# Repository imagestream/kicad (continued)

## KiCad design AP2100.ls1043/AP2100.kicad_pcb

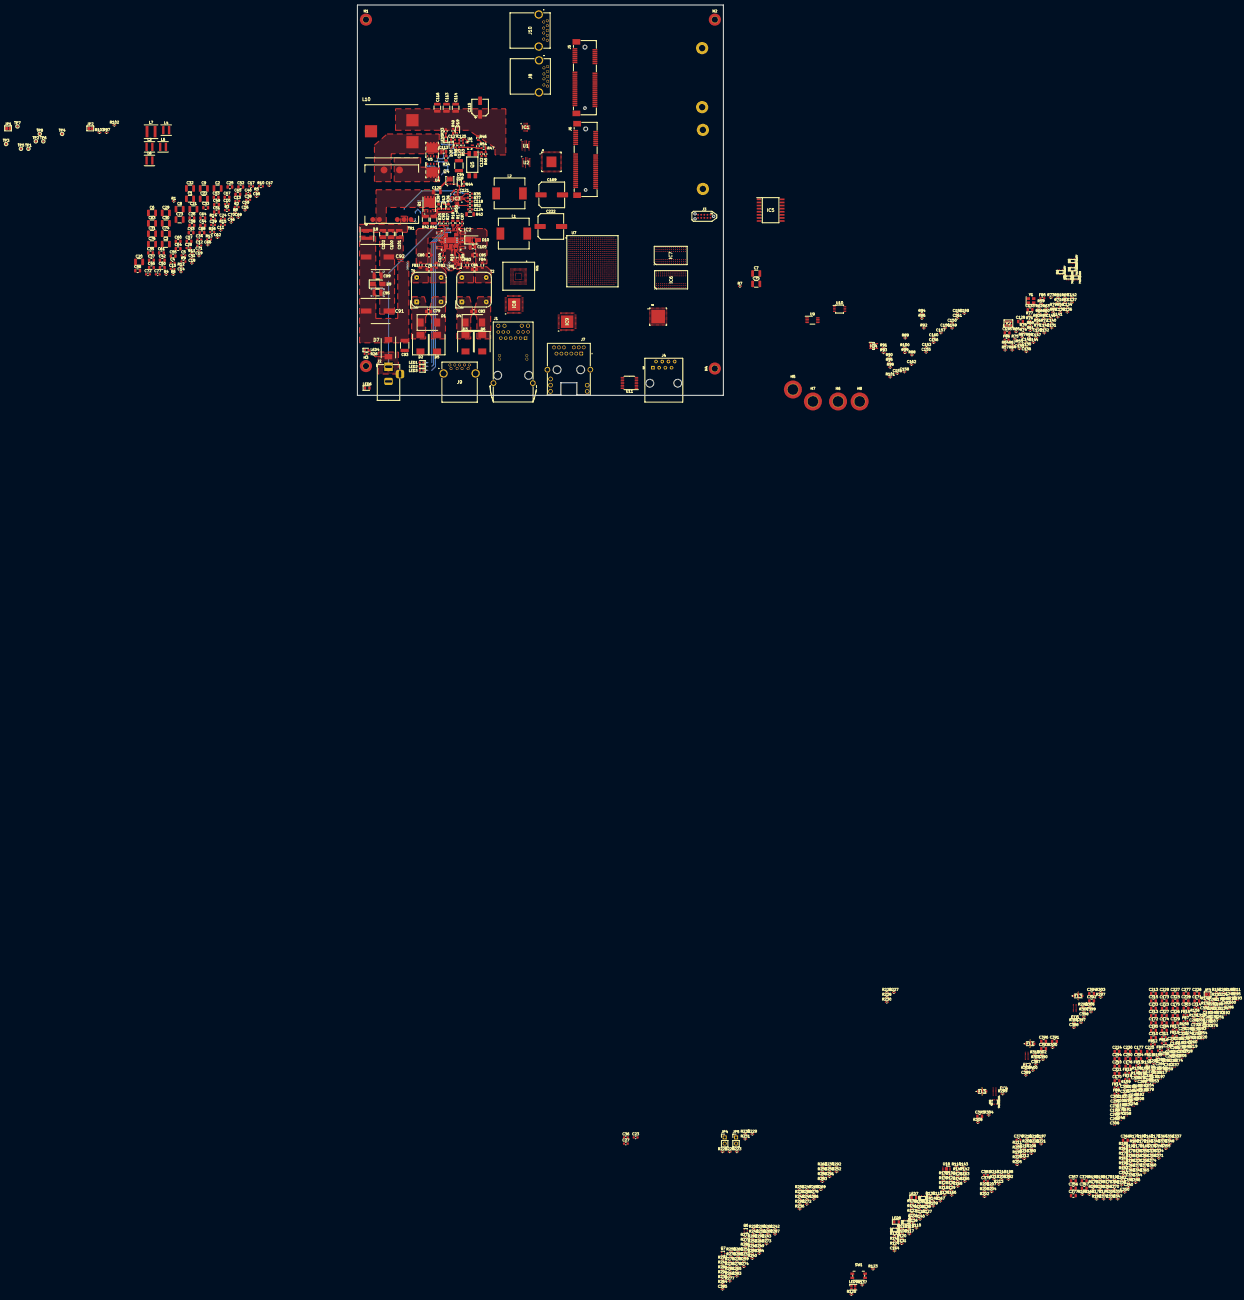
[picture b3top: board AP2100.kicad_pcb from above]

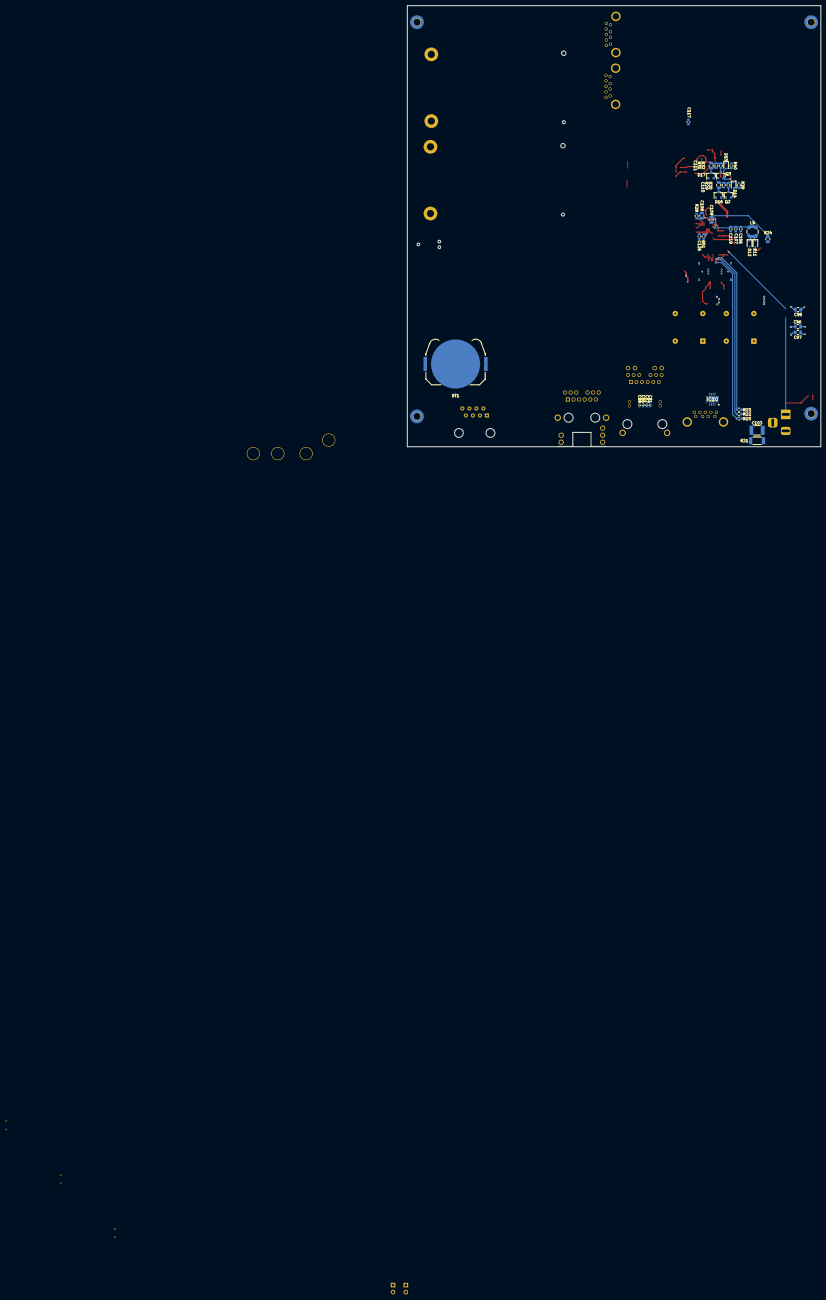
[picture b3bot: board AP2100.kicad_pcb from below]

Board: 6 copper layers, 150.0 x 160.0 mm, 854 parts (41 on the bottom side), 547 nets.

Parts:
BT1: CR2032; BatteryHolder_Keystone_3034_1x20mm
C1, C2, C3, C6, C7, C20, C21, C22, C29, C30, C73, C74: 22uF; C_1210_3225Metric
C4, C5, C12, C13, C15, C24, C28, C38, C39, C40, C72: .1uF; C_0603_1608Metric
C8, C9, C31, C32, C75: 100uF; C_1210_3225Metric
C10, C34: 500pF; C_0603_1608Metric
C11, C14, C16, C19, C69, C70, C135, C137, C139, C141, C331, C332, C333, C334: 1uF; C_0402_1005Metric
C17, C311, C314: .47uF; C_0603_1608Metric
C18: .22uF; C_0402_1005Metric
C23, C27, C36: 47uF; C_0603_1608Metric
C25, C26, C33, C42, C43, C44, C45, C60, C61, C310, C313, C366: 4.7uF; C_0805_2012Metric
C35, C37: DNS 4.7uF; C_0805_2012Metric
C41, C46, C47, C48, C59, C62, C66, C71, C81, C82, C86, C88, C129, C130, C131, C132, C134, C136, C138, C140, C142, C149, C151, C152, C153, C154, C155, C156, C157, C158, C159, C160, C161, C162, C163, C164, C165, C166, C167, C168, C335, C336, C337, C338, C339, C340, C341, C342, C343, C344, C345, C346, C347, C348, C349, C350, C351, C352, C353, C354, C355, C358, C359, C360, C361, C362, C363, C364, C365, C368, C369, C370, C371, C372, C373, C374, C375, C380, C382, C383, C384, C385, C386, C387, C388, C389, C390, C397, C398, C399, C400: .1uF; C_0402_1005Metric
C49, C50, C51, C52, C53, C54, C55, C56, C57, C58, C64, C65, C67, C68, C170, C171, C172, C173, C174, C175, C176, C177, C184, C185, C210, C223, C224, C225, C226, C227, C228, C229, C230, C233, C250, C277, C294, C303, C304, C315, C326, C391, C393, C395: 22uF; C_0805_2012Metric
C63, C76: 2.2uF; C_1210_3225Metric
C77: 5600pF; C_0603_1608Metric
C78, C80, C84, C85: 33nF; C_0805_2012Metric
C79, C83, C97, C98, C108, C109, C112: 1nF; C_0805_2012Metric
C87, C89, C118: 10nF; C_0603_1608Metric
C90: 1nF; C_0603_1608Metric
C91, C92: 33uF; CAPAE1030X1050N
C93, C103: 2.2nF; C_1812_4532Metric
C94: 2200pF; C_1812_4532Metric
C95, C99, C100, C101, C102: 4.7uF; C_1210_3225Metric
C96: 100nF; C_0805_2012Metric
C104: 1.5nF; C_0603_1608Metric
C105: 10nF; C_0805_2012Metric
C106, C127: 2.2uF 25V; C_0603_1608Metric
C107, C117, C119, C121, C122, C126: 100nF; C_0603_1608Metric
C110, C111: 100pF; C_0805_2012Metric
C113, C114, C116: 47uF; C_1210_3225Metric
C115: 100uF; CP_Elec_6.3x5.9
C120: 47nF; C_1206_3216Metric
C123: 220pF; C_0603_1608Metric
C124: 100pF; C_0603_1608Metric
C125: 22nF; C_0603_1608Metric
C128, C133, C213, C321, C323, C327, C329, C356, C357, C367, C376, C377, C392, C394, C396: 10uF; C_0805_2012Metric
C143, C144: 6.8pF; C_0402_1005Metric
C145: DNS 10uF; C_0805_2012Metric
C146, C147, C148: DNS .1uF; C_0402_1005Metric
C150: 1000pF; C_0402_1005Metric
C169, C222: 470uF; C_Elec_10x10.2
C178, C179, C180, C181, C182, C183, C186, C187, C188, C189, C190, C191, C192, C193, C194, C195, C196, C197, C198, C199, C200, C201, C202, C203, C204, C205, C206, C207, C208, C209, C211, C212, C214, C218, C219, C220, C221, C231, C232, C237, C238, C239, C240, C241, C242, C243, C244, C245, C246, C247, C249, C254, C255, C256, C257, C258, C259, C260, C261, C262, C263, C264, C265, C266, C267, C268, C269, C270, C271, C273, C274, C275, C278, C279, C284, C285, C286, C287, C288, C289, C290, C291, C295, C296, C300, C301, C307, C308, C316, C317, C318, C325: .1uF; C_0201_0603Metric
C215, C216, C217, C234, C235, C236, C248, C251, C252, C253, C272, C276, C283: 1500pF; C_0201_0603Metric
C280, C281, C293, C298, C302, C305, C320: 2.2uF; C_0402_1005Metric
C282, C297, C299, C306, C309, C312, C319: 3000pF; C_0402_1005Metric
C292: 1500pF; C_0402_1005Metric
C322, C324, C328, C330: 1uF; C_0201_0603Metric
C378, C379, C381: 2.2uF; C_0603_1608Metric
D1, D2, D3, D4, D5, D6: SM15T68CA; D_SMC
D7: STPS4S200S; DIOM8059X265N
D8: BAV70; SOT-23
D9, D10: SMAJ58A; D_SMA
D11, D12, D13, D14, D15: BAS16J; D_SOD-323
D16: BZX84C10LT1G; SOT-23
D17: BZX84C10; SOT-23
D18, D19, D20: BAS70; D_SOD-323
FB1, FB2, FB3, FB4: 220 OHM; L_0805_2012Metric
FB5: 600 OHM 500mA; L_0603_1608Metric
FB6: DNS 120 OHM 3A; L_0603_1608Metric
FB7, FB8, FB9, FB10, FB11, FB12, FB13, FB14, FB15, FB16, FB17, FB18, FB19: 120 OHM 3A; L_0603_1608Metric
FL1, FL3, FL5: NFE31PT222Z1E9L; NFE31
FL2, FL4, FL6: ACM2012-900-2P-T002; ACM2012_1
H1, H2, H3, H4: Mounting Hole; MountingHole_2.5mm_Pad_TopBottom
H5, H6, H7, H8: FlatAntenna; MountingHole_4.4mm_Pad_TopOnly
IC1: MAX17632BATE+; QFN50P300X300X80-17N
IC2: PM8805TR
IC3: PM8804TR; QFN50P340X340X90-17N
IC4: MIC2774N-29YM5-TR; SOT95P280X145-5N
IC5: PCF2129T_2,518; SOIC127P1032X265-16N
IC6, IC7: AS4C256M16D4-75BCN; BGA96C80P9X16_750X1350X120
IC8, IC9: KSZ9131RNXC; QFN50P700X700X90-49N
IC10: MAX1564ETE+; QFN65P400X400X80-17N
J1: 0826-1X1T-GH-F; BEL_0826-1X1T-GH-F
J2: Barrel_Jack; BarrelJack_Horizontal
J3: Conn_ARM_JTAG_SWD_10; Tag-Connect_TC2050-IDC-NL_2x05_P1.27mm_Vertical
J4: RJ45; RJ45_Amphenol_54602-x08_Horizontal
J5, J6: Bus_PCI_Express_Mini; BUS_PCI_Express_Mini_Full
J7: L836-1J1T-43; BEL_L836-1J1T-43
J8, J9, J10: SS-52000-001; SS52000001
JP1, JP2, JP3: SolderJumper_2_Open; SolderJumper-2_P1.3mm_Open_TrianglePad1.0x1.5mm
JP4, JP5: Jumper_2_Open; PinHeader_1x02_P2.54mm_Vertical
L1, L2: .56uH; L_13.5x12.5mm_H6mm
L3, L5, L6: 1.5uH; L_Coilcraft_XxL4040
L4: 0.6uH; L_Coilcraft_XxL4040
L7: 10uH; L_Coilcraft_XAL5030
L8: 5.6uH; L_Coilcraft_XAL5030
L9: 1mH; L_Coilcraft_LPS4018
L10: 10uH; WE-HCF_201322
LED1: T2; LED_0603_1608Metric
LED2: T1; LED_0603_1608Metric
LED3: T0; LED_0603_1608Metric
LED4: AUX; LED_0603_1608Metric
LED5: +12V; LED_0603_1608Metric
LED6: PWRLED; LED_0805_2012Metric
LED7: WIFI1_LED; LED_0805_2012Metric
LED8: WIFI2_LED; LED_0805_2012Metric
LED9: STATUS LED; LED_Cree-PLCC4_2x2mm_CW
Q1: BSC190N15NS3GATMA1; TRANS_BSC100N06LS3GATMA1
Q2, Q3: PBSS4240T; SOT-23
Q4: FDMC86259P; FDMC86160
Q5: FOD817AS; SOP254P1016X385-4N
Q6, Q7: NTA4151P; SOT-416
R1: 50K; R_0402_1005Metric
R2, R13, R27, R28, R33, R39, R40, R44: 10K; R_0603_1608Metric
R3: 90K; R_0603_1608Metric
R4, R5, R7, R81, R82, R86, R91, R107, R108, R114, R115, R122, R197, R198, R199, R200, R201, R202, R203, R204, R205, R206, R226, R231, R247, R253, R254, R255, R259, R279, R283, R284, R285, R288: 10K; R_0402_1005Metric
R6, R8, R77, R78, R103, R104, R105, R106, R123, R125, R126, R127, R128, R131, R133, R134, R138, R139, R140, R143, R145, R191, R223, R224, R227, R228, R229, R232, R233, R269, R297, R303, R306: 0; R_0402_1005Metric
R9, R15: 30.1K; R_0603_1608Metric
R10, R16: 6.98K; R_0603_1608Metric
R11: 499K; R_0402_1005Metric
R12, R248, R280, R298, R299: 100K; R_0402_1005Metric
R14: 3.74K; R_0603_1608Metric
R17: 36.5; R_0805_2012Metric
R18: 150; R_0805_2012Metric
R19: 26.1K; R_0603_1608Metric
R20, R22, R23: 3.9K; R_0603_1608Metric
R21: 0; R_2010_5025Metric
R24, R36: 10; R_0805_2012Metric
R25: 100K; R_0603_1608Metric
R26, R53: 4.7K; R_0603_1608Metric
R29, R31: 1K; R_0603_1608Metric
R30, R32: 22; R_0603_1608Metric
R34: 18; R_0805_2012Metric
R35: 91K; R_0603_1608Metric
R37: 330K; R_0603_1608Metric
R38: 10K; R_0805_2012Metric
R41: 0R05; R_1210_3225Metric
R42: R100; R_1210_3225Metric
R43: 0; R_1206_3216Metric
R45, R46: 0; R_0603_1608Metric
R47: 20K; R_0603_1608Metric
R48, R50: 2K; R_0603_1608Metric
R49: 47K; R_0603_1608Metric
R51: 390; R_0603_1608Metric
R52: 130K; R_0603_1608Metric
R54: 5.23K; R_0603_1608Metric
R55, R75: 82; R_0402_1005Metric
R56, R76, R85: 110; R_0402_1005Metric
R57, R58, R59, R60, R61, R63, R72, R73, R158, R159: 10; R_0402_1005Metric
R62, R70, R71, R74: 1; R_0402_1005Metric
R64, R65, R66, R67, R68, R69: 49.9; R_0402_1005Metric
R79, R80: 33; R_0402_1005Metric
R83: 75; R_0402_1005Metric
R84: 56; R_0402_1005Metric
R87: DNS 10K; R_0402_1005Metric
R88, R89, R90, R97, R100, R102, R109, R110, R111, R112, R113, R116, R117, R120, R135, R171, R179, R187, R208, R210, R211, R212, R213, R214, R215, R217, R218, R220, R234, R235, R239, R240, R252, R260: 4.7K; R_0402_1005Metric
R92, R93, R94, R95, R96, R98, R101, R119, R129, R221, R222, R245, R249, R265, R266, R267, R277, R281, R293, R294, R296, R301, R304, R307, R309, R310: 1K; R_0402_1005Metric
R99, R118: DNP 4.7K; R_0402_1005Metric
R121, R130, R132: DNP 0; R_0402_1005Metric
R124, R137: 91K; R_0402_1005Metric
R136, R148, R149, R150, R151, R154: 330; R_0402_1005Metric
R141, R142, R144, R146, R147, R243, R244, R275, R276: 220; R_0402_1005Metric
R152, R153: 0R33; R_0402_1005Metric
R155, R156, R157, R160: 5.1; R_0402_1005Metric
R161, R162: 240; R_0402_1005Metric
R163, R164: 36; R_0402_1005Metric
R165, R166, R167, R168, R169, R170, R172, R173, R174, R176, R177, R178, R180, R181, R182, R183, R185, R186, R188, R189, R190, R192, R193, R194, R195, R196: 39; R_0402_1005Metric
R175, R184: 162; R_0402_1005Metric
R207, R209, R216: DNS 4.7K; R_0402_1005Metric
R219: 2K; R_0402_1005Metric
R225, R230: 2.7K; R_0402_1005Metric
R236, R237, R238, R241, R242, R246, R270, R271, R272, R273, R274, R278: 22; R_0402_1005Metric
R250: 698; R_0402_1005Metric
R251, R302, R305, R308: 200; R_0402_1005Metric
R256, R257, R258, R286, R287, R289: DNP 10K; R_0402_1005Metric
R261, R282: 6.04K; R_0402_1005Metric
R262, R263, R264, R268, R290, R291, R292, R295: DNP 1K; R_0402_1005Metric
R300: 26.1K; R_0402_1005Metric
SW1: RESET; Panasonic_EVQPUJ_EVQPUA
T1, T2: RN102-2-02-1M1; Choke_Schaffner_RN102-04-14.0x14.0mm
TP1, TP2, TP3, TP4, TP5, TP6, TP7, TP8: TestPoint; TestPoint_Pad_D1.0mm
TR1: POE120PL-12L; Transformer_Coilcraft_POE120PL
U1, U2: MPQ8634AGLE-P; QFN45P300X400X100-21N
U3: MC34VR500V4ES; QFN50P800X800X90-57N
U4, U5: STL90N6F7; TRANS_STL60P4LLF6
U6: TS2431-AILT; SOT-23-3
U7: LS1043ASE7xxx; BGA621C80P25X25_2100X2100X192N
U8: 6V49205BNLGI; QFP50P700X700X90-49N
U9: 74LVC2G08; VSSOP-8_3.0x3.0mm_P0.65mm
U10: SA56004EDP,118; TSSOP-8_3x3mm_P0.65mm
U11: SP3232EBEY-L/TR; TSSOP-16_4.4x5mm_P0.65mm
U12, U13, U16, U19: 74LVC1G08; SC70
U14, U15, U17, U20: 74LVC1G07; SC70
U18: ATECC608A-MAHDA; DFN-8-1EP_3x2mm_P0.5mm_EP1.3x1.5mm
U21: EMMC04G-M627-A01; BGA153N50P14X14_1300X1150X100N
U22: 74LVC2G04; SC70-6
U23, U24, U25: SP3011; uDFN-14_1.35x3.5mm_P0.5mm
Y1: 25 MHz; Crystal_SMD_3225-4Pin_3.2x2.5mm
Y2: DNS AX3DAF1-156.2500; AX3DCF11562500

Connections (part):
/1V5: C53.2, C54.2, C55.2, C56.2, C57.2, C58.2, J5.6 (+1V5), J5.28 (+1V5), J5.48 (+1V5), J6.6 (+1V5), J6.28 (+1V5), J6.48 (+1V5), L4.1, U3.13 (FB1)
/1V8: C67.2, C68.2, C151.1, C161.1, C162.1, C163.1, C164.1, C166.1, C167.1, C168.1, C178.2, C179.2, C180.2, C181.2, C182.2, C183.2, C184.2, C185.2, C209.2, C210.2, C212.1, C213.2, C379.2, C380.1, FB7.1, FB8.1, FB19.1, J3.1 (VTref), JP1.1, JP2.2, L6.1, R88.1, R89.1, R90.1, R91.2, R96.1, R97.1, R98.1, R100.2, R101.2, R107.2, R108.2, R109.2, R110.2, R111.2, R112.2, R113.2, R114.2, R115.2, R116.2, R117.2, R118.1, R119.2, R122.2, R129.2, R137.2, R149.1, R155.1, R156.1, R157.1, R160.1, R197.1, R198.1, R199.1, R200.1, R201.1, R202.1, R203.1, R204.1, R205.1, R206.1, R207.1, R208.1, R209.1, R221.1, R222.1, U3.25 (FB2), U7.J12 (OVDD1), U7.J13 (OVDD2), U7.J14 (OVDD3)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
/2V5_VPP: C33.2, C331.1, C332.1, C333.1, C334.1, IC6.B1 (VPP_1), IC6.R9 (VPP_2), IC7.B1 (VPP_1), IC7.R9 (VPP_2), U3.28 (LDO3)
/3V3: C11.2, C14.2, C23.2, C27.2, C28.2, C29.2, C30.2, C31.2, C32.2, C34.1, C36.2, C41.2, C42.2, C43.2, C44.2, C45.2, C46.2, C47.2, C48.2, C59.2, C60.2, C61.2, C62.2, C134.1, C149.1, C152.1, C157.1, C158.1, C160.1, C165.1, C231.2, C232.2, C233.2, C381.2, C382.1, C387.1, FB5.2, FB6.1, FB17.1, FB18.1, IC4.5 (VDD), IC5.16 (VDD), IC8.1 (AVDDH_1), IC8.12 (AVDDH_2), IC8.16 (DVDDH_1), IC8.34 (DVDDH_2), IC8.40 (DVDDH_3), IC9.1 (AVDDH_1), IC9.12 (AVDDH_2), IC9.16 (DVDDH_1), IC9.34 (DVDDH_2), IC9.40 (DVDDH_3), J1.18 (LEDY+), J1.19 (LEDG-_O+), J5.2 (+3V3AUX), J5.24 (+3V3AUX), J5.39 (+3V3AUX), J5.41 (+3V3AUX), J5.52 (+3V3AUX), J6.2 (+3V3AUX), J6.24 (+3V3AUX), J6.39 (+3V3AUX), J6.41 (+3V3AUX), J6.52 (+3V3AUX), J7.14, J7.16, L2.2, LED9.4 (A), Q6.2 (S), Q7.2 (S), R4.2, R5.1, R13.2, R81.1, R82.1, R92.2, R93.2, R94.2, R95.2, R124.2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
/3V3_PG: R126.1, U2.9 (PGOOD)
/5V: C73.1, C74.1, C75.2, C390.1, IC1.6 (FB), IC1.9 (EXTVCC), IC10.1 (INA), IC10.2 (VCC), IC10.3 (INB), IC10.4 (INC), IC10.5 (SEL), JP4.2 (B), JP5.2 (B), L7.2
/5V_PG: IC1.8 (~RESET), R127.1
/12V: C1.1, C2.1, C3.1, C20.1, C21.1, C22.1, C63.1, C113.1, C114.1, C115.1, C116.1, C117.1, D19.1 (K), IC1.1 (EN/UVLO), IC1.15 (VIN_1), IC1.16 (VIN_2), L10.2, R11.2, R33.2, R46.1, R49.2, U1.10 (VIN_1), U1.21 (VIN_2), U2.10 (VIN_1), U2.21 (VIN_2)
/25MHZ_CPLD: R83.2, R85.2
/25MHZ_EC1_RGMII: IC8.46 (XI), R80.2
/25MHZ_EC2_RGMII: IC9.46 (XI), R79.2
/125M_CLK: R84.2, U7.AA3 (EC1_GTX_CLK125), U7.AE4 (EC2_GTX_CLK125)
/CPU Power/EVDD: C249.2, C250.2, FB7.2, U7.M8 (EVDD)
/CPU_VDD_PG: R125.1, U1.9 (PGOOD)
/CPU_VDD_SENSE: C5.2, C6.2, C7.2, C8.2, C9.2, C10.1, C215.2, C216.2, C217.2, C218.2, C219.2, C220.2, C221.2, C222.1, C223.2, C224.2, C225.2, C226.2, C227.2, C228.2, C229.2, C230.2, C234.2, C235.2, C236.2, C237.2, C238.2, C239.2, C240.2, C241.2, C242.2, C243.2, C244.2, C245.2, C246.2, C247.2, C248.2, C251.2, C252.2, C253.2, C254.2, C255.2, C256.2, C257.2, C258.2, C259.2, C260.2, C261.2, C262.2, C263.2, C264.2, C265.2, C266.2, C267.2, C268.2, C269.2, C270.2, C271.2, C272.2, C315.2, C316.2, FB9.1, FB11.1, FB13.1, FB14.1, FB15.1, FB16.1, JP3.2 (B), L1.2, R2.2, R102.1, R154.2, R159.2, U7.H20 (TA_BB_VDD), U7.K13 (VDD01), U7.K15 (VDD02), U7.K17 (VDD03), U7.L10 (VDD04), U7.L12 (VDD05), U7.L14 (VDD06)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
/DDR4 Memory/ALERT_B: IC6.P9 (ALERT#), IC7.P9 (ALERT#), R191.2
/DDR4 Memory/DDR4_A0: IC6.P3 (A0), IC7.P3 (A0), R168.1, U7.AC25 (D1_MA00)
/DDR4 Memory/DDR4_A1: IC6.P7 (A1), IC7.P7 (A1), R169.1, U7.AA21 (D1_MA01)
/DDR4 Memory/DDR4_A2: IC6.R3 (A2), IC7.R3 (A2), R170.1, U7.V23 (D1_MA02)
/DDR4 Memory/DDR4_A3: IC6.N7 (A3), IC7.N7 (A3), R172.1, U7.AD23 (D1_MA03)
/DDR4 Memory/DDR4_A4: IC6.N3 (A4), IC7.N3 (A4), R173.1, U7.AA23 (D1_MA04)
/DDR4 Memory/DDR4_A5: IC6.P8 (A5), IC7.P8 (A5), R174.1, U7.W23 (D1_MA05)
/DDR4 Memory/DDR4_A6: IC6.P2 (A6), IC7.P2 (A6), R176.1, U7.AC24 (D1_MA06)
/DDR4 Memory/DDR4_A7: IC6.R8 (A7), IC7.R8 (A7), R177.1, U7.U24 (D1_MA07)
/DDR4 Memory/DDR4_A8: IC6.R2 (A8), IC7.R2 (A8), R178.1, U7.R22 (D1_MA08)
/DDR4 Memory/DDR4_A9: IC6.R7 (A9), IC7.R7 (A9), R180.1, U7.W22 (D1_MA09)
/DDR4 Memory/DDR4_A10: IC6.M3 (A10/AP), IC7.M3 (A10/AP), R181.1, U7.AB23 (D1_MA10)
/DDR4 Memory/DDR4_A11: IC6.T2 (A11), IC7.T2 (A11), R182.1, U7.T23 (D1_MA11)
/DDR4 Memory/DDR4_A12: IC6.M7 (A12/BC#), IC7.M7 (A12/BC#), R183.1, U7.AC23 (D1_MA12)
/DDR4 Memory/DDR4_A13: IC6.T8 (A13), IC7.T8 (A13), R185.1, U7.T25 (D1_MA13)
/DDR4 Memory/DDR4_A15: IC6.L3 (ACT#), IC7.L3 (ACT#), R186.1, U7.U21 (D1_MA15/!MACT)
/DDR4 Memory/DDR4_BA0: IC6.N2 (BA0), IC7.N2 (BA0), R165.1, U7.AC21 (D1_MBA0)
/DDR4 Memory/DDR4_BA1: IC6.N8 (BA1), IC7.N8 (BA1), R166.1, U7.Y23 (D1_MBA1)
/DDR4 Memory/DDR4_BA2: IC6.M2 (BG0), IC7.M2 (BG0), R167.1, U7.AE23 (D1_MBA2/MBG0)
/DDR4 Memory/DDR4_CAS_B: IC6.M8 (CAS#/A15), IC7.M8 (CAS#/A15), R189.1, U7.AC22 (~D1_MCAS~)
/DDR4 Memory/DDR4_CKE0: IC6.K2 (CKE), IC7.K2 (CKE), R192.1, U7.W21 (D1_MCKE0)
/DDR4 Memory/DDR4_CKE1: R193.1, U7.AB21 (D1_MCKE1)
/DDR4 Memory/DDR4_CLK_N: IC6.K8 (CK#), IC7.K8 (CK#), R163.1, U7.AA25 (~D1_MCK0~)
/DDR4 Memory/DDR4_CLK_P: IC6.K7 (CK), IC7.K7 (CK), R164.1, U7.AA24 (D1_MCK0)
/DDR4 Memory/DDR4_CS0_B: IC6.L7 (CS#), IC7.L7 (CS#), R195.1, U7.U23 (~D1_MCS0~)
/DDR4 Memory/DDR4_DM0: IC6.E7 (LDM#/LDBI#), U7.L25 (D1_MDM0)
/DDR4 Memory/DDR4_DM1: IC6.E2 (UDM#/UDBI#), U7.L21 (D1_MDM1)
/DDR4 Memory/DDR4_DM2: IC7.E7 (LDM#/LDBI#), U7.E23 (D1_MDM2)
/DDR4 Memory/DDR4_DM3: IC7.E2 (UDM#/UDBI#), U7.G23 (D1_MDM3)
/DDR4 Memory/DDR4_DQ0: IC6.G2 (DQ0), U7.J25 (D1_MDQ00)
/DDR4 Memory/DDR4_DQ1: IC6.F7 (DQ1), U7.K24 (D1_MDQ01)
/DDR4 Memory/DDR4_DQ2: IC6.H3 (DQ2), U7.N24 (D1_MDQ02)
/DDR4 Memory/DDR4_DQ3: IC6.H7 (DQ3), U7.R24 (D1_MDQ03)
/DDR4 Memory/DDR4_DQ4: IC6.H2 (DQ4), U7.H24 (D1_MDQ04)
/DDR4 Memory/DDR4_DQ5: IC6.H8 (DQ5), U7.K25 (D1_MDQ05)
/DDR4 Memory/DDR4_DQ6: IC6.J3 (DQ6), U7.N25 (D1_MDQ06)
/DDR4 Memory/DDR4_DQ7: IC6.J7 (DQ7), U7.P25 (D1_MDQ07)
/DDR4 Memory/DDR4_DQ8: IC6.A3 (DQ8), U7.L23 (D1_MDQ08)
/DDR4 Memory/DDR4_DQ9: IC6.B8 (DQ9), U7.M23 (D1_MDQ09)
/DDR4 Memory/DDR4_DQ10: IC6.C3 (DQ10), U7.N21 (D1_MDQ10)
/DDR4 Memory/DDR4_DQ11: IC6.C7 (DQ11), U7.P21 (D1_MDQ11)
/DDR4 Memory/DDR4_DQ12: IC6.C2 (DQ12), U7.K21 (D1_MDQ12)
/DDR4 Memory/DDR4_DQ13: IC6.C8 (DQ13), U7.L22 (D1_MDQ13)
/DDR4 Memory/DDR4_DQ14: IC6.D3 (DQ14), U7.M21 (D1_MDQ14)
/DDR4 Memory/DDR4_DQ15: IC6.D7 (DQ15), U7.P23 (D1_MDQ15)
/DDR4 Memory/DDR4_DQ16: IC7.G2 (DQ0), U7.C24 (D1_MDQ16)
/DDR4 Memory/DDR4_DQ17: IC7.F7 (DQ1), U7.C25 (D1_MDQ17)
/DDR4 Memory/DDR4_DQ18: IC7.H3 (DQ2), U7.F24 (D1_MDQ18)
/DDR4 Memory/DDR4_DQ19: IC7.H7 (DQ3), U7.H25 (D1_MDQ19)
/DDR4 Memory/DDR4_DQ20: IC7.H2 (DQ4), U7.B24 (D1_MDQ20)
/DDR4 Memory/DDR4_DQ21: IC7.H8 (DQ5), U7.D24 (D1_MDQ21)
/DDR4 Memory/DDR4_DQ22: IC7.J3 (DQ6), U7.F25 (D1_MDQ22)
/DDR4 Memory/DDR4_DQ23: IC7.J7 (DQ7), U7.G25 (D1_MDQ23)
/DDR4 Memory/DDR4_DQ24: IC7.A3 (DQ8), U7.F22 (D1_MDQ24)
/DDR4 Memory/DDR4_DQ25: IC7.B8 (DQ9), U7.H21 (D1_MDQ25)
/DDR4 Memory/DDR4_DQ26: IC7.C3 (DQ10), U7.J23 (D1_MDQ26)
/DDR4 Memory/DDR4_DQ27: IC7.C7 (DQ11), U7.K23 (D1_MDQ27)
/DDR4 Memory/DDR4_DQ28: IC7.C2 (DQ12), U7.G21 (D1_MDQ28)
/DDR4 Memory/DDR4_DQ29: IC7.C8 (DQ13), U7.F23 (D1_MDQ29)
/DDR4 Memory/DDR4_DQ30: IC7.D3 (DQ14), U7.J21 (D1_MDQ30)
/DDR4 Memory/DDR4_DQ31: IC7.D7 (DQ15), U7.J22 (D1_MDQ31)
/DDR4 Memory/DDR4_DQS0_N: IC6.F3 (LDQS#), U7.M25 (~D1_MDQS0~)
/DDR4 Memory/DDR4_DQS0_P: IC6.G3 (LDQS), U7.M24 (D1_MDQS0)
/DDR4 Memory/DDR4_DQS1_N: IC6.A7 (UDQS#), U7.N23 (~D1_MDQS1~)
/DDR4 Memory/DDR4_DQS1_P: IC6.B7 (UDQS), U7.N22 (D1_MDQS1)
/DDR4 Memory/DDR4_DQS2_N: IC7.F3 (LDQS#), U7.D25 (~D1_MDQS2~)
/DDR4 Memory/DDR4_DQS2_P: IC7.G3 (LDQS), U7.E25 (D1_MDQS2)
/DDR4 Memory/DDR4_DQS3_N: IC7.A7 (UDQS#), U7.H22 (~D1_MDQS3~)
/DDR4 Memory/DDR4_DQS3_P: IC7.B7 (UDQS), U7.H23 (D1_MDQS3)
/DDR4 Memory/DDR4_ODT0: IC6.K3 (ODT), IC7.K3 (ODT), R194.1, U7.U22 (D1_MODT0)
/DDR4 Memory/DDR4_PAR: IC6.T3 (PAR), IC7.T3 (PAR), R196.1, U7.U25 (D1_MAPAR_OUT)
/DDR4 Memory/DDR4_RAS_B: IC6.L8 (RAS#/A16), IC7.L8 (RAS#/A16), R190.1, U7.AB25 (~D1_MRAS~)
/DDR4 Memory/DDR4_TEN: IC6.N9 (TEN), IC7.N9 (TEN), R179.1
/DDR4 Memory/DDR4_WE_B: IC6.L2 (WE#/A14), IC7.L2 (WE#/A14), R188.1, U7.Y21 (~D1_MWE~)
/DDR4_RST_B: IC6.P1 (RESET#), IC7.P1 (RESET#), R139.2, R171.2
/DDRCLK_18: R75.2, R76.2, U7.F19 (DDRCLK)
/DDR_VREF: C69.2, C336.1, C337.1, C338.1, C339.1, IC6.M1 (VREFCA), IC7.M1 (VREFCA), U3.31 (REFOUT)
/DDR_VTT: C64.2, C65.2, C340.1, C341.1, C342.1, C343.1, C344.1, C345.1, C346.1, C347.1, C358.1, C359.1, C360.1, C361.1, C362.1, C363.1, C364.1, C365.1, C366.1, C367.1, L5.1, R165.2, R166.2, R167.2, R168.2, R169.2, R170.2, R172.2, R173.2, R174.2, R176.2, R177.2, R178.2, R180.2, R181.2, R182.2, R183.2, R185.2, R186.2, R188.2, R189.2, R190.2, R192.2, R193.2, R194.2, R195.2, R196.2, U3.19 (FB4)
/DIFF_SYSCLK_N: R73.2, U7.G9 (~DIFF_SYSCLK~)
/DIFF_SYSCLK_P: R72.2, U7.G8 (DIFF_SYSCLK)
/ETH0_LED1-: J1.20 (LEDG+_O-), R243.2
/ETH0_LED2-: J1.17 (LEDY-), R244.2
/Flash / eMMC/IFC_CLE: R207.2, R219.2, U7.C19 (CFG_RCW_SRC8/IFC_CLE)
/GVDD: C49.2, C50.2, C51.2, C52.2, C66.1, C70.2, C169.1, C170.2, C171.2, C172.2, C173.2, C174.2, C175.2, C176.2, C177.2, C186.2, C187.2, C188.2, C189.2, C190.2, C191.2, C192.2, C193.2, C194.2, C195.2, C196.2, C197.2, C198.2, C199.2, C200.2, C201.2, C202.2, C203.2, C204.2, C205.2, C206.2, C207.2, C208.2, C335.1, C348.1, C349.1, C350.1, C351.1, C352.1, C353.1, C354.1, C355.1, C356.1, C357.1, C368.1, C369.1, C370.1, C371.1, C372.1, C373.1, C374.1, C375.1, C376.1, C377.1, IC6.A1 (VDDQ_1), IC6.A9 (VDDQ_2), IC6.B3 (VDD_1), IC6.B9 (VDD_2), IC6.C1 (VDDQ_3), IC6.D1 (VDD_3), IC6.D9 (VDDQ_4), IC6.F2 (VDDQ_5), IC6.F8 (VDDQ_6), IC6.G1 (VDDQ_7), IC6.G7 (VDD_4), IC6.G9 (VDDQ_8), IC6.J1 (VDD_5), IC6.J2 (VDDQ_9), IC6.J8 (VDDQ_10), IC6.J9 (VDD_6), IC6.L1 (VDD_7), IC6.L9 (VDD_8), IC6.R1 (VDD_9), IC6.T9 (VDD_10), IC7.A1 (VDDQ_1)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
/I2C1_SCL: R8.2, R77.1, R93.1, R103.1, R131.1, R145.1, U7.N1 (IIC1_SCL)
/I2C1_SDA: R6.2, R78.1, R92.1, R104.1, R134.1, R143.1, U7.M1 (IIC1_SDA)
/I2C2_SCL: R95.1, R224.1, U7.K3 (GPIO4_02/IIC2_SCL)
/I2C2_SDA: R94.1, R223.1, U7.L3 (GPIO4_03/IIC2_SDA)
/I2C4_SCL: R229.1, R309.1, U7.M3 (GPIO4_12/USB3_DRWBUS)
/I2C4_SDA: R228.1, R310.1, U7.N3 (GPIO4_13/USB3_PWRFAULT)
/MPCIE0_CLK_N: J5.11 (REFCLK-), R58.2, R67.2
/MPCIE0_CLK_P: J5.13 (REFCLK+), R57.2, R66.2
/MPCIE1_CLK_N: J6.11 (REFCLK-), R60.2, R69.2
/MPCIE1_CLK_P: J6.13 (REFCLK+), R59.2, R68.2
/PMIC_INT_B: R4.1, U3.1 (~INT~), U9.2
/PMIC_POR_B: R130.1, R138.1, U3.3 (~POR~)
/POE_TD1_N: IC8.3 (TXRXM_A), J1.10 (TRD1-)
/POE_TD1_P: IC8.2 (TXRXP_A), J1.11 (TRD1+)
/POE_TD2_N: IC8.6 (TXRXM_B), J1.5 (TRD2-)
/POE_TD2_P: IC8.5 (TXRXP_B), J1.4 (TRD2+)
/POE_TD3_N: IC8.8 (TXRXM_C), J1.2 (TRD3-)
/POE_TD3_P: IC8.7 (TXRXP_C), J1.3 (TRD3+)
/POE_TD4_N: IC8.11 (TXRXM_D), J1.9 (TRD4-)
/POE_TD4_P: IC8.10 (TXRXP_D), J1.8 (TRD4+)
/PWR_X1VDD: C25.2, C294.2, C303.2, C304.2, FB10.2, FB12.2, U3.18 (LDO1)
/PoE Power/IN_12: C80.1, FB1.2, IC2.12 (IN12_1), IC2.15 (IN12_2), IC2.16 (IN12_3), IC2.EP4
/PoE Power/IN_36: C80.2, FB2.2, IC2.19 (IN36_1), IC2.20 (IN36_2), IC2.23 (IN36_3), IC2.EP3
/PoE Power/IN_45: C85.1, FB3.2, IC2.33 (IN45_1), IC2.36 (IN45_2), IC2.37 (IN45_3), IC2.EP2
/PoE Power/IN_78: C85.2, FB4.2, IC2.1 (IN78_1), IC2.40 (IN78_2), IC2.41 (IN78_3), IC2.EP1
/PoE Power/PGD: C108.1, IC2.25 (PGD), IC3.6 (PGD), R28.2
/PoE Power/VB: C87.1, IC2.2 (VB), LED1.2 (A), LED2.2 (A), LED3.2 (A), R28.1
/PoE Power/VDC: C91.1, C92.1, C93.1, C95.1, C96.1, C97.1, C98.1, C99.1, D7.1, D8.2 (A), D9.1 (K), IC2.27 (VOUT_1), IC2.28 (VOUT_2), L8.1
/PoE Power/VOB: C89.2, C105.1, D8.1 (A), D10.1 (A1), IC2.17 (VOB_1), IC2.18 (VOB_2), IC2.29 (VOB_3), IC2.30 (VDD), IC2.38 (VOB_4), IC2.39 (VOB_5), IC2.EP5, IC2.EP6, R19.1
/Power/EN_VDD: C26.2, R1.1, U3.26 (LDO2)
/RST_PCIE0_B: R227.1, U17.4
/RST_PCIE1_B: R232.1, U20.4
/RST_eMMC_B: R140.2, R197.2, U21.K5 (RST_N)
/Reset/JTAG_RST_B_18: J3.10 (~RESET~), R114.1, U13.2
/Reset/PORESET_B_18: R121.1, R137.1, U7.F10 (~PORESET~), U13.4, U14.2, U15.2, U16.1, U19.1
/Reset/RESET_BTN_B: R91.1, SW1.1 (A), U7.L1 (GPIO1_20/!UART2_RTS)
/Reset/RESET_REQ_B_18: R97.2, R128.2, U7.G7 (~RESET_REQ~)
/Reset/RST_PCIE0: U7.K1 (GPIO1_18/UART2_SIN), U16.2
/Reset/RST_PCIE1: U7.L2 (GPIO1_16/UART2_SOUT), U19.2
/Reset/RTC_OUT: IC5.7 (CLKOUT), R129.1, U7.F16 (RTC/GPIO1_14)
/Reset/TABB_RTCCLK: TP2.1, U7.G20 (TA_BB_RTC)
/Reset/THERM_INTn: U9.1, U9.3
/Reset/UART_CTS: U7.J1 (GPIO1_21/!UART1_CTS), U11.9 (R2OUT)
/Reset/UART_RTS: U7.J2 (GPIO1_19/!UART1_RTS), U11.10 (T2IN)
/Reset/UART_RX: U7.H2 (GPIO1_17/UART1_SIN), U11.12 (R1OUT)
/Reset/UART_TX: U7.H1 (GPIO1_15/UART1_SOUT), U11.11 (T1IN)
/S1VDD: C280.2, C281.2, C282.2, C283.2, C284.2, C285.2, C286.2, C287.2, C288.2, FB9.2, FB11.2, R251.1, U7.T15 (S1VDD1), U7.T16 (S1VDD2), U7.T17 (S1VDD3), U7.T18 (S1VDD4), U7.W14 (S1VDD5)
/SD1_REFCLK1_N: C147.2, R240.1, U7.W9 (SD1_REF_CLK1_N)
/SD1_REFCLK1_P: C148.2, R239.1, U7.W10 (SD1_REF_CLK1_P)
/SD1_REFCLK2_N: R63.2, R65.2, U7.AD20 (SD1_REF_CLK2_N)
/SD1_REFCLK2_P: R61.2, R64.2, U7.AE20 (SD1_REF_CLK2_P)
/SD_RX1_N: J5.23 (PERn0), U7.AD15 (SD1_RX1_N)
/SD_RX1_P: J5.25 (PERp0), U7.AE15 (SD1_RX1_P)
/SD_RX2_N: J6.23 (PERn0), U7.AD17 (SD1_RX2_N)
/SD_RX2_P: J6.25 (PERp0), U7.AE17 (SD1_RX2_P)
/SD_TX1_N: J5.31 (PETn0), U7.AB15 (SD1_TX1_N)
/SD_TX1_P: J5.33 (PETp0), U7.AA15 (SD1_TX1_P)
/SD_TX2_N: J6.31 (PETn0), U7.AB17 (SD1_TX2_N)
/SD_TX2_P: J6.33 (PETp0), U7.AA17 (SD1_TX2_P)
/SOC_IRQ0: IC8.38 (INT_N/PME_N2/ALLPHYAD), R90.2, R245.2, U7.F15 (IRQ00)
/SOC_IRQ1: IC9.38 (INT_N/PME_N2/ALLPHYAD), R89.2, R277.2, U7.G15 (IRQ01)
/SYSCLK_18: R55.2, R56.2, U7.F9 (SYSCLK)
/SerDes / RGMII Ethernet/P0_LED1: IC8.17 (LED1/PME_N1//PHYAD0), R243.1, R259.2, R268.1
/SerDes / RGMII Ethernet/P0_LED2: IC8.15 (LED2/PHYAD1), R244.1, R258.2, R267.1
/SerDes / RGMII Ethernet/P0_RXD0: IC8.32 (RXD0/MODE0), R236.2, R256.2, R265.1
/SerDes / RGMII Ethernet/P0_RXD1: IC8.31 (RXD1/MODE1), R237.2, R255.2, R264.1
/SerDes / RGMII Ethernet/P0_RXD2: IC8.28 (RXD2/MODE2), R238.2, R254.2, R263.1
/SerDes / RGMII Ethernet/P0_RXD3: IC8.27 (RXD3/MODE3), R241.2, R253.2, R262.1
/SerDes / RGMII Ethernet/P0_RX_CLK: IC8.35 (RXC/PHYAD2), R246.2, R257.2, R266.1
/SerDes / RGMII Ethernet/P0_RX_CTL/CLK125_EN: IC8.33 (RX_CTL/CLK125_EN), R242.2, R249.1
/SerDes / RGMII Ethernet/P1_LED1: IC9.17 (LED1/PME_N1//PHYAD0), R275.1, R289.2, R296.1
/SerDes / RGMII Ethernet/P1_LED2: IC9.15 (LED2/PHYAD1), R276.1, R288.2, R295.1
/SerDes / RGMII Ethernet/P1_RXD0: IC9.32 (RXD0/MODE0), R270.2, R286.2, R293.1
/SerDes / RGMII Ethernet/P1_RXD1: IC9.31 (RXD1/MODE1), R271.2, R285.2, R292.1
/SerDes / RGMII Ethernet/P1_RXD2: IC9.28 (RXD2/MODE2), R272.2, R284.2, R291.1
/SerDes / RGMII Ethernet/P1_RXD3: IC9.27 (RXD3/MODE3), R273.2, R283.2, R290.1
/SerDes / RGMII Ethernet/P1_RX_CLK: IC9.35 (RXC/PHYAD2), R278.2, R287.2, R294.1
/SerDes / RGMII Ethernet/P1_RX_CTL/CLK125_EN: IC9.33 (RX_CTL/CLK125_EN), R274.2, R281.1
/USB/USB1_DM: FL2.3, J8.3 (D+), U23.6, U23.9
/USB/USB1_DP: FL2.4, J8.2 (D-), U23.7, U23.8
/USB/USB1_PWR: C391.2, C392.2, FL1.1, FL3.1, FL5.1, IC10.12 (OUTA), R297.1, R303.1, R306.1
/USB/USB1_RXDM: J8.5 (SSRX-), U7.E4 (USB1_RX_M), U23.1, U23.14
/USB/USB1_RXDP: J8.6 (SSRX+), U7.E3 (USB1_RX_P), U23.2, U23.13
/USB/USB1_TXDM: C389.2, J8.8 (SSTX-), U23.3, U23.12
/USB/USB1_TXDP: C388.2, J8.9 (SSTX+), U23.4, U23.11
/USB/USB2PWR_FLT: U7.M4 (GPIO4_11/USB2_PWRFAULT), U22.4
/USB/USB2_DM: FL4.3, J9.3 (D+), U24.6, U24.9
/USB/USB2_DP: FL4.4, J9.2 (D-), U24.7, U24.8
/USB/USB2_PWR: C393.2, C394.2, IC10.10 (OUTB)
/USB/USB2_PWREN: IC10.15 (ONB), U7.L4 (GPIO4_10/USB2_DRWBUS)
/USB/USB2_RXDM: J9.5 (SSRX-), U7.C4 (USB2_RX_M), U24.1, U24.14
/USB/USB2_RXDP: J9.6 (SSRX+), U7.C3 (USB2_RX_P), U24.2, U24.13
/USB/USB2_TXDM: C398.2, J9.8 (SSTX-), U24.3, U24.12
/USB/USB2_TXDP: C397.2, J9.9 (SSTX+), U24.4, U24.11
/USB/USB3_DM: FL6.3, J10.3 (D+), U25.6, U25.9
/USB/USB3_DP: FL6.4, J10.2 (D-), U25.7, U25.8
/USB/USB3_PWR: C395.2, C396.2, IC10.9 (OUTC)
/USB/USB3_RXDM: J10.5 (SSRX-), U7.A4 (USB3_RX_M), U25.1, U25.14
/USB/USB3_RXDP: J10.6 (SSRX+), U7.A3 (USB3_RX_P), U25.2, U25.13
/USB/USB3_TXDM: C400.2, J10.8 (SSTX-), U25.3, U25.12
/USB/USB3_TXDP: C399.2, J10.9 (SSTX+), U25.4, U25.11
/USB/USB13PWR_FLT: U7.G6 (GPIO4_30/USB1_PWRFAULT), U22.6
/USB/USB13_PWREN: IC10.14 (ONC), IC10.16 (ONA), U7.H6 (GPIO4_29/USB_DRVVBUS)
/X1VDD: C289.2, C290.2, C291.2, C292.2, C293.2, C295.2, C296.2, C297.2, C302.2, FB10.1, FB12.1, R152.2, R153.2, R250.1, U7.W15 (X1VDD1), U7.W16 (X1VDD2), U7.W17 (X1VDD3), U7.W18 (X1VDD4), U7.Y19 (X1VDD5)
Earth: C81.1, C82.1, C86.1, C88.1, C93.2, C103.1, D2.1 (A1), D3.2 (A2), D5.1 (A1), D6.2 (A2), J1.21 (SHIELD), J1.22 (SHIELD), R21.2
GND: BT1.2 (-), C1.2, C2.2, C3.2, C5.1, C6.1, C7.1, C8.1, C9.1, C11.1, C12.2, C13.2, C14.1, C15.1, C16.1, C17.1, C18.1, C19.1, C20.2, C21.2, C22.2, C23.1, C25.1, C26.1, C27.1, C28.1, C29.1, C30.1, C31.1, C32.1, C33.1, C35.1, C36.1, C37.1, C38.2, C39.2, C40.1, C41.1, C42.1, C43.1, C44.1, C45.1, C46.1, C47.1, C48.1, C49.1, C50.1, C51.1, C52.1, C53.1, C54.1, C55.1, C56.1, C57.1, C58.1, C59.1, C60.1, C61.1, C62.1, C63.2, C64.1, C65.1, C67.1, C68.1, C69.1, C70.1, C71.1, C73.2, C74.2, C75.1, C76.2, C77.2, C94.2, C113.2, C114.2, C115.2, C116.2, C117.2, C122.1, C127.2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
GNDA: C109.2, C118.1, C124.1, C126.1, IC3.1 (AGND), IC3.17 (EP), Q5.3, R35.1, R37.1, R43.2, R52.1
GNDPWR: C87.2, C90.2, C91.2, C92.2, C94.1, C95.2, C96.2, C97.2, C98.2, C99.2, C100.2, C101.2, C102.2, C103.2, C104.1, C105.2, C106.2, C107.2, C108.2, C119.2, D9.2 (A), D10.2 (A2), D12.2 (A), D18.1 (K), IC2.3 (STBY), IC2.6 (AGND), IC2.10 (FAUX), IC2.13 (GND12_1), IC2.14 (GND12_2), IC2.21 (GND36_1), IC2.22 (GND36_2), IC2.34 (GND45_1), IC2.35 (GND45_2), IC2.42 (GND78_1), IC2.43 (GND78_2), IC3.10 (PGND), J2.2, Q4.1 (S_1), Q4.2 (S_2), Q4.3 (S_3), R17.2, R18.2, R21.1, R26.2, R27.2, R38.1, R41.1, R42.1, R43.1, R44.1, TR1.1
unnamed: BT1.1 (+), C159.1, R133.2
unnamed: C4.1, L1.1, U1.20 (SW)
unnamed: C4.2, U1.1 (BST)
unnamed: C10.2, R2.1, R3.2, U1.7 (FB)
unnamed: C12.1, U1.19 (VCC)
unnamed: C13.1, C15.2, U1.5 (TRK/REF)
unnamed: C16.2, U3.51 (VDIG)
unnamed: C17.2, U3.43 (VBIAS)
unnamed: C18.2, U3.52 (VBG)
unnamed: C19.2, U3.49 (VCC)
unnamed: C24.1, L2.1, U2.20 (SW)
unnamed: C24.2, U2.1 (BST)
unnamed: C34.2, R13.1, R14.2, U2.7 (FB)
unnamed: C35.2, U3.39 (LDO4)
unnamed: C37.2, U3.41 (LDO5)
unnamed: C38.1, U2.19 (VCC)
unnamed: C39.1, C40.2, U2.5 (TRK/REF)
unnamed: C66.2, C71.2, U3.29 (VHALF)
unnamed: C72.1, IC1.11 (LX_1), IC1.12 (LX_2), L7.1
unnamed: C72.2, IC1.10 (BST)
unnamed: C76.1, IC1.2 (VCC)
unnamed: C77.1, IC1.5 (SS)
unnamed: C78.1, FB1.1, T1.2
unnamed: C78.2, FB2.1, T1.4
unnamed: C79.1, D1.1 (A1), D2.2 (A2), J1.13 (VC1), T1.1
unnamed: C79.2, D1.2 (A2), D5.2 (A2), J1.14 (VC2), T1.3
unnamed: C81.2, J1.12 (TRCT1)
unnamed: C82.2, J1.6 (TRCT2)
unnamed: C83.1, D3.1 (A1), D4.1 (A1), J1.15 (VC3), T2.1
unnamed: C83.2, D4.2 (A2), D6.1 (A1), J1.16 (VC4), T2.3
unnamed: C84.1, FB3.1, T2.2
unnamed: C84.2, FB4.1, T2.4
unnamed: C86.2, J1.1 (TRCT3)
unnamed: C88.2, J1.7 (TRCT4)
unnamed: C89.1, D8.3 (K), IC2.32 (VCP)
unnamed: C90.1, IC2.11 (RAUX), R25.1, R27.1
unnamed: C100.1, C101.1, C102.1, L8.2, R24.2, TR1.5
unnamed: C104.2, IC2.24 (CTRL)
unnamed: C106.1, C107.1, C119.1, IC3.12 (VC), L9.1
unnamed: C109.1, IC3.8 (VIN), R24.1
unnamed: C110.1, C112.1, D14.1 (K), L10.1, R29.1, R30.1, TR1.10, U5.5 (D_1), U5.6 (D_2), U5.7 (D_3), U5.8 (D_4)
unnamed: C110.2, D16.3 (K), Q2.1 (B), R29.2
unnamed: C111.1, D15.1 (K), R31.1, R32.1, TR1.8, U4.5 (D_1), U4.6 (D_2), U4.7 (D_3), U4.8 (D_4)
unnamed: C111.2, D17.3 (K), Q3.1 (B), R31.2
unnamed: C112.2, R34.1
unnamed: C118.2, IC3.2 (SS)
unnamed: C120.1, Q4.5 (D_1), Q4.6 (D_2), Q4.7 (D_3), Q4.8 (D_4)
unnamed: C120.2, Q1.5 (D_1), Q1.6 (D_2), Q1.7 (D_3), Q1.8 (D_4), TR1.2
unnamed: C121.1, D18.2 (A), Q4.4 (G), R44.2
unnamed: C121.2, IC3.11 (GAT2)
unnamed: C122.2, Q5.1, R45.2
unnamed: C123.1, R47.1, R53.1, R54.1, U6.2 (REF)
unnamed: C123.2, C125.2, D20.2 (A), R48.1, U6.1 (K)
unnamed: C124.2, IC3.14 (CS), R50.2
unnamed: C125.1, R53.2
unnamed: C126.2, R51.2
unnamed: C127.1, D19.2 (A), D20.1 (K), R49.1
unnamed: C128.2, C129.1, C130.1, C131.1, C132.1, C133.2, FB5.1, R62.1, R70.1, R71.1, R74.1, U8.7 (VDD_REF1), U8.19 (VDD_2P048), U8.27 (VDD_PCIE), U8.43 (VDD_DDR), U8.48 (VDD_REF2)
unnamed: C135.1, C136.1, R62.2, U8.42 (AVDD_SYS)
unnamed: C137.1, C138.1, R70.2, U8.33 (AVDD_PCIE)
unnamed: C139.1, C140.1, R71.2, U8.20 (AVDD_125)
unnamed: C141.1, C142.1, R74.2, U8.12 (AVDD12_24)
unnamed: C143.2, U8.2 (X1_25), Y1.3
unnamed: C144.2, U8.1 (X2_25), Y1.1
unnamed: C145.2, C146.1, FB6.2, R87.2, Y2.6 (VDD)
unnamed: C147.1, Y2.5 (CLK#)
unnamed: C148.1, Y2.4 (CLK)
unnamed: C150.1, U7.R6 (TD1_ANODE), U10.2 (D+)
unnamed: C150.2, U7.P6 (TD1_CATHODE), U10.3 (D-)
unnamed: C153.1, U11.1 (C1+)
unnamed: C153.2, U11.3 (C1-)
unnamed: C154.1, U11.4 (C2+)
unnamed: C154.2, U11.5 (C2-)
unnamed: C155.1, U11.2 (VS+)
unnamed: C156.1, U11.6 (VS-)
unnamed: C211.2, JP1.2, R148.2, U7.G14 (PROG_MTR)
unnamed: C214.2, JP2.1, R150.2, U7.F14 (TA_PROG_SEP)
unnamed: C273.2, C274.2, C275.2, C276.2, C277.2, FB8.2, U7.U12 (LVDD1), U7.U13 (LVDD2), U7.U14 (LVDD3)
unnamed: C278.2, C279.2, JP3.1 (A), R151.2, U7.R7 (FA_VL)
unnamed: C298.2, C299.2, C300.2, C301.2, FB13.2, FB14.2, U7.J10 (USB_SVDD1), U7.J11 (USB_SVDD2)
unnamed: C305.2, C306.2, C307.2, C308.2, FB15.2, FB16.2, U7.K9 (USB_SDVDD1), U7.K11 (USB_SDVDD2)
unnamed: C309.2, C310.2, C311.2, R152.1, U7.W12 (AVDD_SD1_PLL1)
unnamed: C312.2, C313.2, C314.2, R153.1, U7.V19 (AVDD_SD1_PLL2)
unnamed: C317.2, C318.2, C319.2, C320.2, FB17.2, FB18.2, U7.J8 (USB_HVDD1), U7.J9 (USB_HVDD2)
unnamed: C321.2, C322.2, R155.2, U7.G12 (AVDD_CGA1)
unnamed: C323.2, C324.2, R156.2, U7.G11 (AVDD_CGA2)
unnamed: C325.2, C326.2, FB19.2, U7.V6 (TVDD)
unnamed: C327.2, C328.2, R157.2, U7.G13 (AVDD_PLAT)
unnamed: C329.2, C330.2, R160.2, U7.T19 (AVDD_D1)
unnamed: C335.2, R163.2, R164.2
unnamed: C378.2, U21.C2 (VCCI)
unnamed: C383.2, J7.12 (TRCT1)
unnamed: C384.2, J7.6 (TRCT2)
unnamed: C385.2, J7.1 (TRCT3)
unnamed: C386.2, J7.7 (TRCT4)
unnamed: C388.1, U7.F1 (USB1_TX_P)
unnamed: C389.1, U7.F2 (USB1_TX_M)
unnamed: C397.1, U7.D1 (USB2_TX_P)
unnamed: C398.1, U7.D2 (USB2_TX_M)
unnamed: C399.1, U7.B1 (USB3_TX_P)
unnamed: C400.1, U7.B2 (USB3_TX_M)
unnamed: D7.2, J2.1, LED4.2 (A), R25.2
unnamed: D11.1 (K), D12.1 (K), L9.2
unnamed: D11.2 (A), TR1.6
unnamed: D13.1 (K), IC3.9 (GAT1), R36.1
unnamed: D13.2 (A), Q1.4 (G), R36.2, R38.2
unnamed: D14.2 (A), Q2.2 (E), R39.2, U4.4 (G)
unnamed: D15.2 (A), Q3.2 (E), R40.2, U5.4 (G)
unnamed: FL1.3, J8.1 (VBUS)
unnamed: FL2.1, U7.E6 (USB1_D_M)
unnamed: FL2.2, U7.F6 (USB1_D_P)
unnamed: FL3.3, J9.1 (VBUS)
unnamed: FL4.1, U7.C6 (USB2_D_M)
unnamed: FL4.2, U7.D6 (USB2_D_P)
unnamed: FL5.3, J10.1 (VBUS)
unnamed: FL6.1, U7.A6 (USB3_D_M)
unnamed: FL6.2, U7.B6 (USB3_D_P)
unnamed: IC2.4 (CLS1), R17.1
unnamed: IC2.5 (CLS2), R18.1
unnamed: IC2.7 (T0), R20.1
unnamed: IC2.8 (T1), R22.1
unnamed: IC2.9 (T2), R23.1
unnamed: IC2.31 (DET), R19.2
unnamed: IC3.3 (DT), R37.2
unnamed: IC3.4 (FSW), R35.2
unnamed: IC3.15 (CTL), Q5.4, R51.1
unnamed: IC3.16 (BLK), R52.2
unnamed: IC4.1 (~RST), R128.1
unnamed: IC4.3 (~MR), R130.2, R135.1, U12.2
unnamed: IC4.4 (IN), R124.1, R125.2, R126.2, R127.2, U12.1
unnamed: IC5.1 (SCL), R131.2
unnamed: IC5.4 (SDA/~CE), R134.2
unnamed: IC5.5 (IFS), IC5.14 (BBS)
unnamed: IC5.15 (VBAT), R133.1
unnamed: IC6.F9 (ZQ), R161.2
unnamed: IC7.F9 (ZQ), R162.2
unnamed: IC8.4 (AVDDL_1), IC8.9 (AVDDL_2), IC8.18 (DVDDL_1), IC8.23 (DVDDL_2), IC8.26 (DVDDL_3), IC8.30 (DVDDL_4), IC8.39 (DVDDL_5), IC8.44 (AVDDL_PLL), Q6.3 (D)
unnamed: IC8.19 (TXD0), U7.Y3 (EC1_TXD0)
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
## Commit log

2020-06-15 Initial commit of Hydroponics and early AP2100
2020-06-15 Add bommgr database - must be symlinked from ~/.bomsaway.d/
2020-06-22 Update AP2100 schematic. Make a copy for FutureElectronics recommendations but going to move quickly with TI solutions.
2020-06-23 Update hydroponics BOM + pdf. Add PM8804/8805 library parts and schematic with them on it
2020-06-26 Add Magjack part
2020-07-07 Update poe Add cap library
2020-07-08 Update PoE section - almost done
2020-07-09 Finish PoE power
2020-07-09 Finish PoE
2020-07-09 Not sure
2020-07-09 Add partsbox.io bom generator script
2020-07-09 Add PartsBox part numbers to everything so far
2020-07-13 More work on memory
2020-07-14 Add + route first 16 memory data lines
2020-07-15 Almost finish memory section
2020-07-15 Finalize DDR4 memory section
2020-07-16 Add new Flat Antenna element 2.4 GHz
2020-07-17 Finalize FlatAnt4x4
2020-09-09 Add emmc library part but likely will delete
2020-09-10 Add 1.2V and 5V power supplies
2020-09-11 Add pmic chip to power section. Finish eMMC.
2020-09-15 Add CPU Power block. Change global labels to hierarchical and link them at top page Add 5V USB power supply
2020-09-16 Add 2nd CPU power page. Start reset block
2020-09-23 Add docs
2020-09-23 Add clocking and start of ethernet
2020-09-24 Finish reset section
2020-09-26 Mostly done with USB - USB1 complete just duplicate to 2+3
2020-09-26 Annotate and update PCB with current design
2020-09-28 RGMII ethernet section almost complete for 1st port Finish USB
2020-09-29 Finish Ethernet all that's left is SerDes
2020-10-01 Review / cleanup footprints, etc
2020-10-01 Added antenna mounting holes
2020-10-05 Added Thermal solutions PDF Fix DDRCLK pulldown
2020-10-06 More cleanups
2020-10-06 More cleanups - fix incorrect serial console pinout Add netclasses
2020-10-08 Add power prototype for initial testing
2020-10-09 Cleanups per ST Micro's review. Add old and old-old kinda by accident
2020-10-15 Layout of PoE up to VDC - going to rework though
2020-10-16 More PoE layout
2020-10-16 Finish Power PoE section layout
2020-10-19 Fixup broken BSC100 footprint with missing pins Add mPCIE footprint with retainer holes Review / complete PartsBox info
2020-10-23 Revise BOM
2020-10-29 Rename AP2100 as AP2100.ls1043 shelving the Layerscape design and starting a new Raspberry Pi 4 compute module based board
2020-10-29 Finish PoE section Rename CM4IO library as AP2100
2020-10-30 Finish PCie routing
2020-11-06 Add AP3000 single radio for security cameras. Add CM4IO Raspi board
2020-11-06 Route all the high speed lines and most gpio
2020-11-10 Forgot to add PCB cutout resulting in some components being moved
2020-11-11 Route more
2020-11-12 Almost done routing!
2020-11-13 Finished routing board.
2020-11-21 AP3000: Fixup PartsBoxID linkage and placed first order Working on a design for a 5 GHz panel antenna array for a point-to-point replacement
2020-11-23 Add RF T and angle footprints
2020-11-23 Finish layout of 4x4 panel - bad ground plane yet
2020-11-25 Finalize flat antenna and reflector. Sent to JLCPCB for fab.
2020-12-21 Finalize 4x4 flat ant and director. Start dual polarity 4x4 antenna
2020-12-24 Rework AP3000 PoE section, power section and change solder paste to -10% overall, -15% for small chips / mpcie and -20% for the raspi connector
2020-12-24 Ordered AP3000 PCBs Ordered FlatAntPanel4x4 PCBs Ordered FlatAntPanel4x4_Reflector PCBs
2020-12-28 Reduce paste and solder mask margins to 0
2021-01-19 Rework AP3000 board - ground planes instead of power planes internal
2021-01-20 Added AP3500 board version to fit in twist-port adaptor
2021-01-22 Almost done with new smaller AP3500 board
2021-01-23 Finalize AP3500 board
2021-01-23 Restore old 4x4 flat antenna. Modify 4 polarity to be 2 pol.
2021-01-23 Add LEDs to AP3000
2021-01-26 Placed AP3000 / AP3500 orders with JLCPCB
2021-02-27 More work on Antennas - laying out the new panel as a 2x2 aperture coupled patch
2021-02-27 Placed an order with JLCPCB for the Tighter 4pol version and the "Dual XPol" which actually was aperture coupled.
2021-03-02 Create AP3000 schematic and PCB PDF as an aid for building boards
2021-03-23 Update JLCPCB components for AP3000
2021-04-01 Fix antenna hole (again?) so that the feed isn't shorted to ground
2021-05-14 Many enhancements to the AP3000 board. Reworking FlatAntPanel4x4 again with proper holes Made a connector test pcb
2021-05-20 Add area for passives to the flatant panel 4x4. Create new single polarity aperture coupled feed antenna
2021-06-11 Add new single polarity aperture coupled 4x4 antenna. RasPiCNM4Connector test Gerbers for PCBWay Cleanups and optimixations for AP3500
2021-06-11 Add dual transformer footprint
2021-06-14 Rework AP3500
2021-06-14 Fix silkscreen
2021-06-19 Updates for JLCPCB components actually in stock at this time
2021-07-12 Finalize the Wurth Transformer Fixup board solving the pin numbering issue
2021-07-14 Update AP3500 with new Wurth footprint - needed rerouted. Fix the gigabit ethernet problem with pair 4 center tap to ground instead of through cap.
2021-07-17 Add AP3100 initial project
2021-09-22 Add first rev of AP2000 motherboard Update libraries - change mPCIE hole size
2021-09-24 Mods to AP2000 for manufacturing. 50 PCBs ordered from JLCPCB with SMd assembly.
2021-09-24 Add top label (AP20000.ai) sent to JRPanel.
2021-09-24 Fix up footprints due to changed components / out of stock components with JLCPCB
2022-03-11 Add notes for the CNC setup
2022-09-03 Added the correct License
